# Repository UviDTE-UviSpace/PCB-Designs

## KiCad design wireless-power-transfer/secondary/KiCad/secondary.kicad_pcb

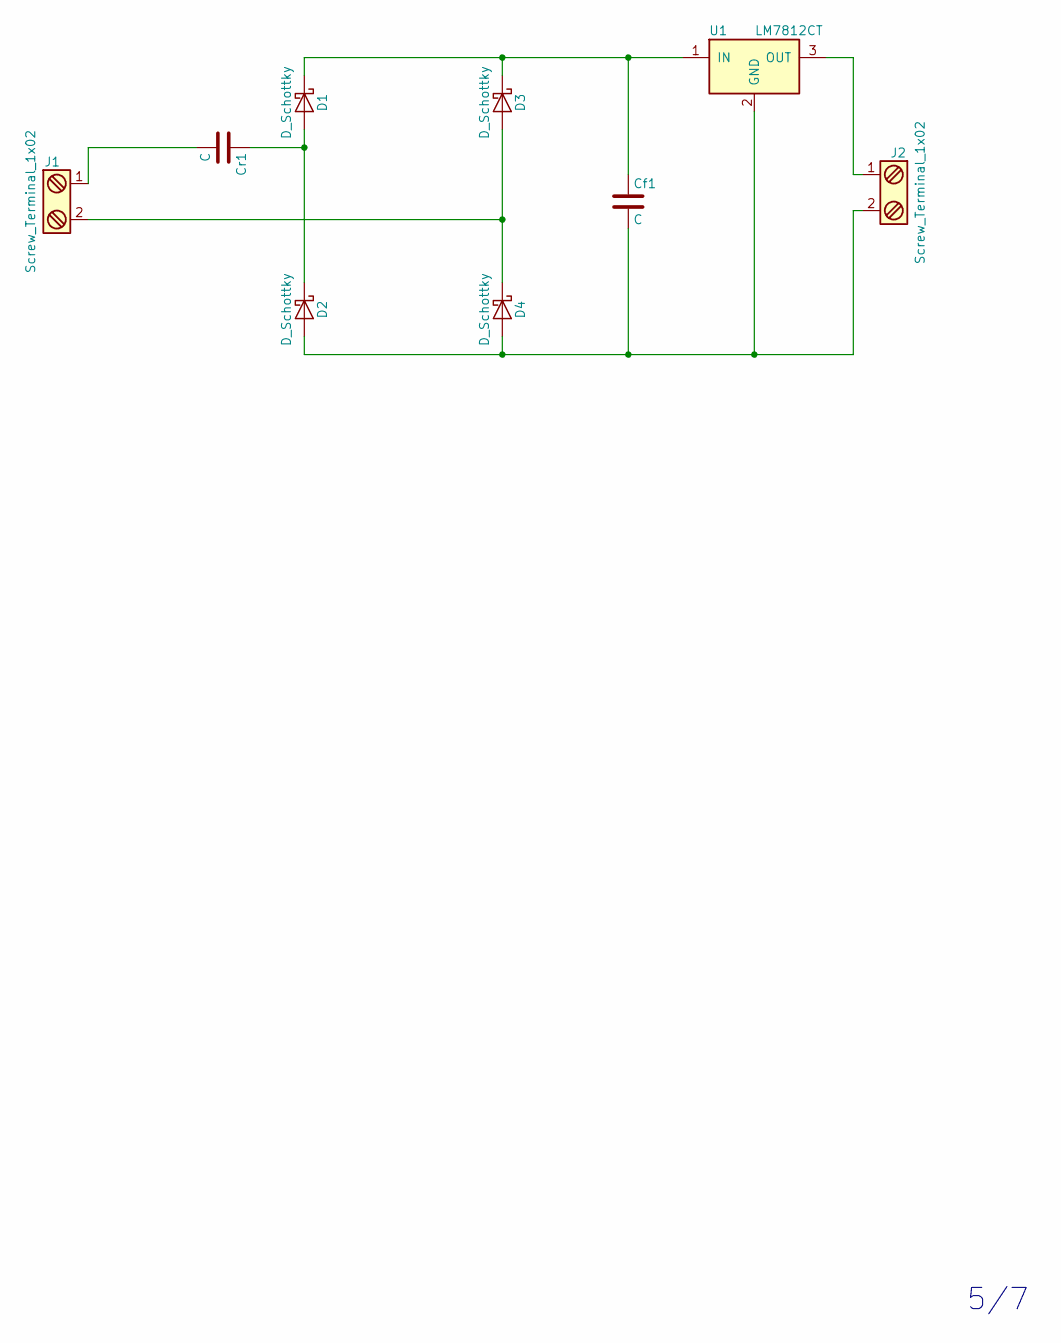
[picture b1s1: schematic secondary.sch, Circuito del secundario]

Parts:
Cf1: C; CP_Radial_D8.0mm_P3.50mm
Cr1: C; C_Axial_L5.1mm_D3.1mm_P7.50mm_Horizontal
D1, D2, D3, D4: D_Schottky; D_DO-201AD_P12.70mm_Horizontal
J1, J2: Screw_Terminal_1x02; TerminalBlock_Pheonix_MKDS1.5-2pol
U1: LM7812CT; TO-220-3_Vertical

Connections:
unnamed: Cf1.1, D1.1 (K), D3.1 (K), U1.1 (IN)
unnamed: Cf1.2, D2.2 (A), D4.2 (A), J2.2, U1.2 (GND)
unnamed: Cr1.1, D1.2 (A), D2.1 (K)
unnamed: Cr1.2, J1.1
unnamed: D3.2 (A), D4.1 (K), J1.2
unnamed: J2.1, U1.3 (OUT)

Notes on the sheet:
5/7

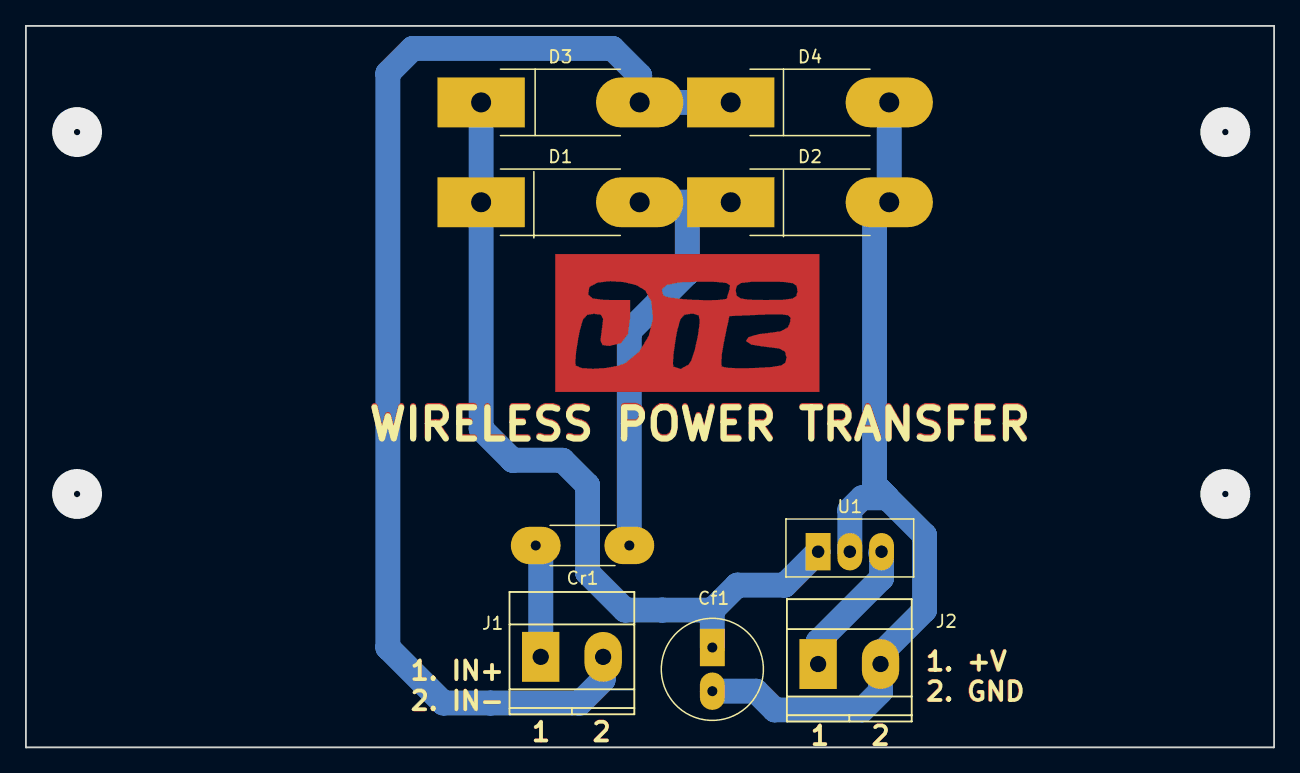
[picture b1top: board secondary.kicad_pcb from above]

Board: 2 copper layers, 100.0 x 57.8 mm, 9 parts (0 on the bottom side), 6 nets.

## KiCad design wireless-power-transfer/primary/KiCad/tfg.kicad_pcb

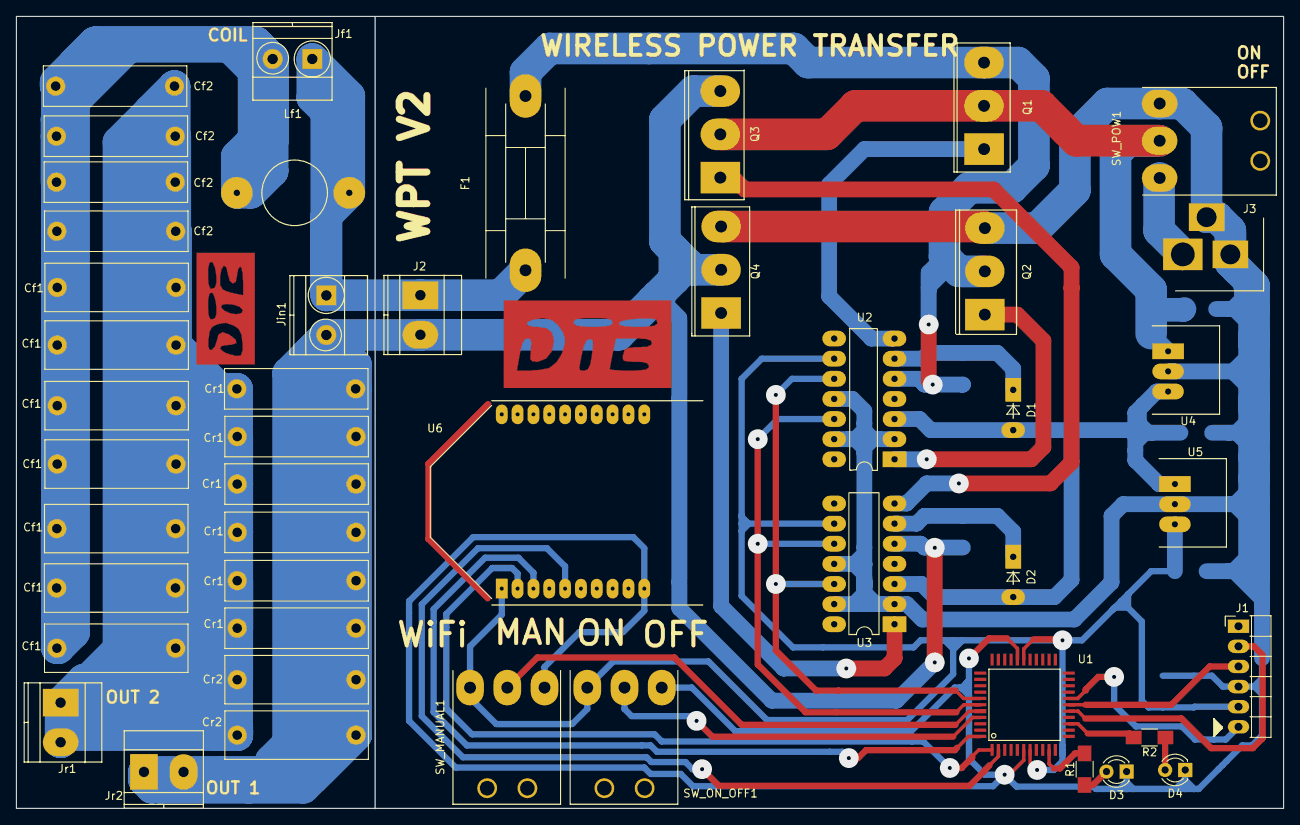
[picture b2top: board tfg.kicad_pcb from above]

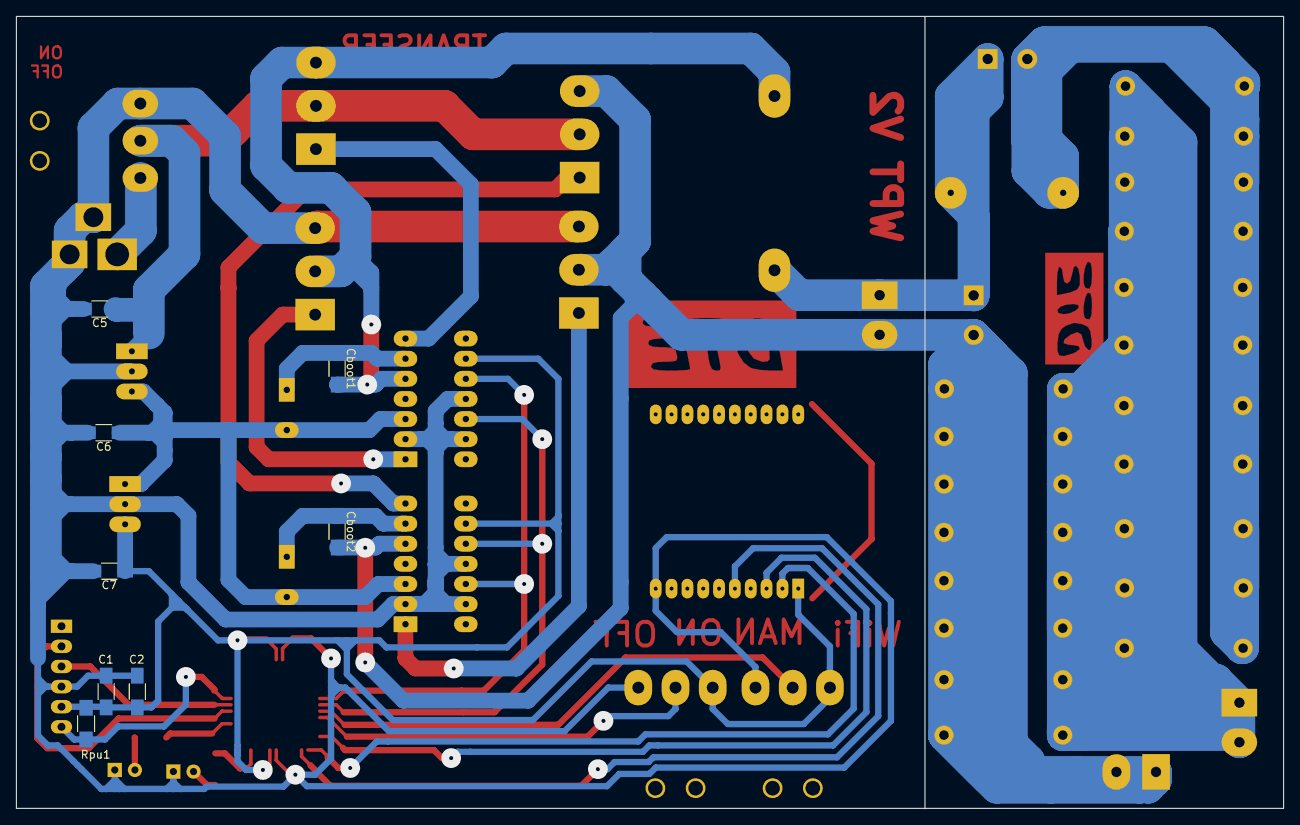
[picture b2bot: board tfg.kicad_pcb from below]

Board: 2 copper layers, 160.0 x 100.0 mm, 55 parts (8 on the bottom side), 31 nets.

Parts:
C1, C2: 0.1uF; C_1206_HandSoldering
C5, C6, C7: 10uF; C_1206_HandSoldering
Cboot1, Cboot2: 0.47uF; C_1206_HandSoldering
Cf1, Cf1#2, Cf1#3, Cf1#4, Cf1#5, Cf1#6, Cf1#7: C; C_Rect_L18.0mm_W6.0mm_P15.00mm_FKS3_FKP3
Cf2, Cf2#2, Cf2#3, Cf2#4: C; C_Rect_L18.0mm_W5.0mm_P15.00mm_FKS3_FKP3
Cr1: C; C_Rect_L18.0mm_W5.0mm_P15.00mm_FKS3_FKP3
Cr1#2, Cr1#3, Cr1#4, Cr1#5, Cr1#6: 100nF; C_Rect_L18.0mm_W5.0mm_P15.00mm_FKS3_FKP3
Cr2: C; C_Rect_L18.0mm_W6.0mm_P15.00mm_FKS3_FKP3
Cr2#2: 10nF; C_Rect_L18.0mm_W6.0mm_P15.00mm_FKS3_FKP3
D1, D2: D; D_DO-35_SOD27_P5.08mm_Vertical_AnodeUp
D3, D4: LED_ALT; LED_D3.0mm
F1: Fuse; Fuseholder5x20_horiz_SemiClosed_Casing10x25mm
J1: CONN_01X06; Pin_Header_Angled_1x06_Pitch2.54mm
J2: Screw_Terminal_1x02; TerminalBlock_Pheonix_MKDS1.5-2pol
J3: BARREL_JACK
Jf1: Screw_Terminal_1x02; TerminalBlock_Pheonix_MKDS1.5-2pol
Jin1: Screw_Terminal_1x02; TerminalBlock_Pheonix_MKDS1.5-2pol
Jr1, Jr2: Screw_Terminal_1x02; TerminalBlock_Pheonix_MKDS1.5-2pol
Lf1: 47uH; MuRata 1500 47u
Q1, Q2, Q3, Q4: IRLB8721PBF; TO-247AC
R1, R2: R; R_1206_HandSoldering
Rpu1: 10k; R_1206_HandSoldering
SW_MANUAL1: SW_SPDT; SPDT_Toggle_Switch
SW_ON_OFF1: SW_SPDT; SPDT_Toggle_Switch
SW_POW1: SW_SPDT; SPDT_Toggle_Switch
U1: PIC18F45K20-I/PT; PIC18F45K20
U2, U3: IR2110; DIP-14_W7.62mm
U4: R-78E15; r-78Exx
U5: R-78E3.3; r-78Exx
U6: XBEE_Wi-Fi; XBee_Wi-Fi

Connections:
/+3.3V: C1.1, C2.1, C7.1, J1.2, Rpu1.2, SW_MANUAL1.1, SW_ON_OFF1.1, U1.7, U1.28, U2.9, U3.9, U5.3, U6.1
/+15V: C6.1, D1.2, D2.2, U2.3, U3.3, U4.3, U5.1
Carga0: Cboot2.2, Cr1.1, Cr2.1, J2.2, Jin1.2, Jr2.1, Jr2.2, Q3.3, Q4.2, U3.5
Carga1: F1.1, J2.1, Jf1.1, Jin1.1, Lf1.1
unnamed: C1.2, C2.2, C5.2, C6.2, C7.2, D3.1, D4.1, J1.3, J3.2, J3.3, Q2.3, Q4.3, SW_MANUAL1.3, SW_ON_OFF1.3, SW_POW1.3, U1.6, U1.29, U2.2, U2.11, U2.13, U3.2, U3.11, U3.13, U4.2, U5.2, U6.10
unnamed: C5.1, Q1.2, Q3.2, SW_POW1.2, U4.1
unnamed: Cboot1.1, D1.1, U2.6
unnamed: Cboot1.2, F1.2, Q1.3, Q2.2, U2.5
unnamed: Cboot2.1, D2.1, U3.6
unnamed: Cf1.1, Cf1#2.1, Cf1#3.1, Cf1#4.1, Cf1#5.1, Cf1#6.1, Cf1#7.1, Cf2.2, Cf2#2.2, Cf2#3.2, Cf2#4.2, Cr1.2, Cr1#2.2, Cr1#3.2, Cr1#4.2, Cr1#5.2, Cr1#6.2, Cr2.2, Cr2#2.2, Jr1.1, Jr1.2
unnamed: Cf1.2, Cf1#2.2, Cf1#3.2, Cf1#4.2, Cf1#5.2, Cf1#6.2, Cf1#7.2, Cf2.1, Cf2#2.1, Cf2#3.1, Cf2#4.1, Jf1.2, Lf1.2
unnamed: Cr1#2.1, Cr1#3.1, Cr1#4.1, Cr1#5.1, Cr1#6.1, Cr2#2.1
unnamed: D3.2, R1.1
unnamed: D4.2, R2.1
unnamed: J1.1, Rpu1.1, U1.18
unnamed: J1.4, U1.17
unnamed: J1.5, U1.16
unnamed: J3.1, SW_POW1.1
unnamed: Q1.1, U2.7
unnamed: Q2.1, U2.1
unnamed: Q3.1, U3.7
unnamed: Q4.1, U3.1
unnamed: R1.2, U1.10
unnamed: R2.2, U1.14
unnamed: SW_MANUAL1.2, U1.40
unnamed: SW_ON_OFF1.2, U1.41
unnamed: U1.1, U6.2
unnamed: U1.2, U6.5
unnamed: U1.38, U2.10, U3.12
unnamed: U1.39, U2.12, U3.10
unnamed: U1.44, U6.3

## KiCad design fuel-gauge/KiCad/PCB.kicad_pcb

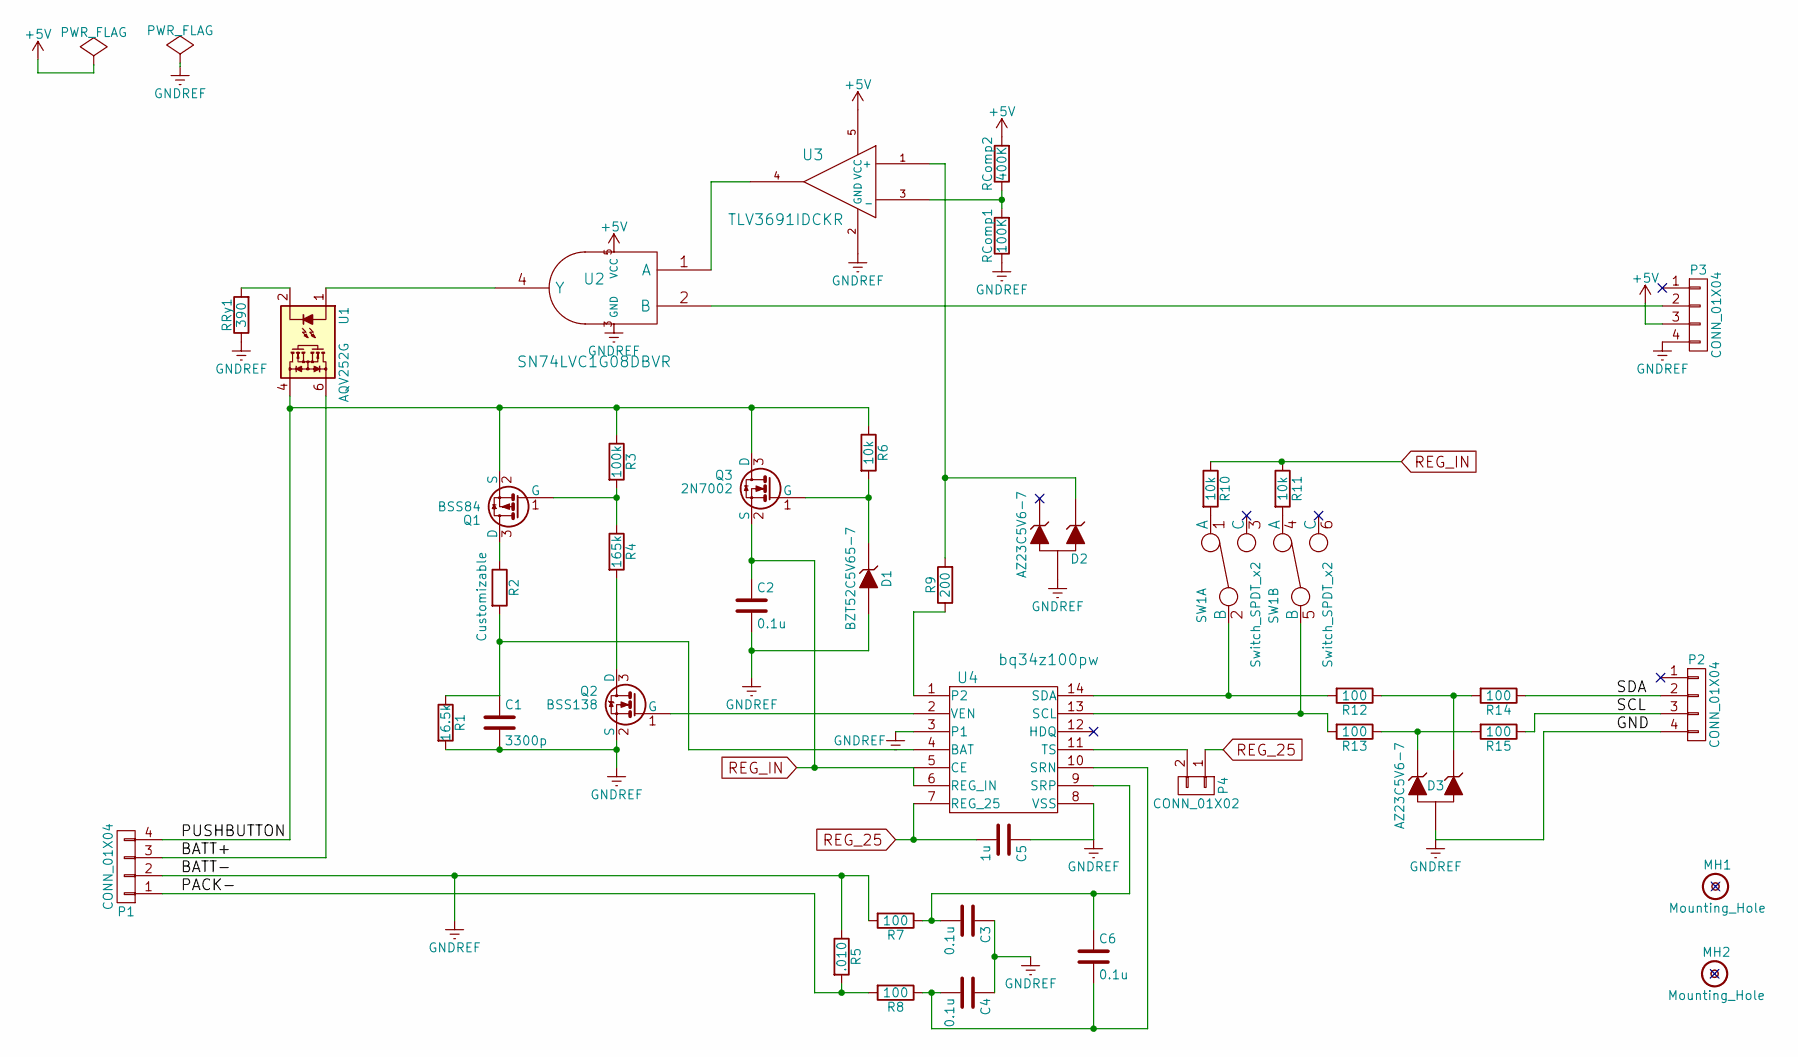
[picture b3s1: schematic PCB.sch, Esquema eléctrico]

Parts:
C1: 3300p; C_0805_HandSoldering
C2, C3, C4, C6: 0.1u; C_0805_HandSoldering
C5: 1u; C_0805_HandSoldering
D1: BZT52C5V65-7; SOD-323
D2, D3: AZ23C5V6-7; D_SOT-23_NKA
MH1, MH2: Mounting_Hole; Mounting_hole
P1, P2, P3: CONN_01X04
P4: CONN_01X02
Q1: BSS84; BSS84-SOT-23_Handsoldering
Q2: BSS138; BSS138-SOT-23_Handsoldering
Q3: 2N7002; SOT-23_Handsoldering
R1: 16.5k; R_0805_My_HandSoldering
R2: Customizable; R_0805_My_HandSoldering
R3: 100k; R_0805_My_HandSoldering
R4: 165k; R_0805_My_HandSoldering
R5: .010; R_2010_My_HandSoldering
R6, R10, R11: 10k; R_0805_My_HandSoldering
R7, R8, R12, R13, R14, R15: 100; R_0805_My_HandSoldering
R9: 200; R_0805_My_HandSoldering
RComp1: 100K; R_0805_My_HandSoldering
RComp2: 400K; R_0805_My_HandSoldering
RRy1: 390; R_0805_My_HandSoldering
SW1: Switch_SPDT_x2; SW1-DIP-8-_6_Handsoldering
U1: AQV252G; DIP-6_W7.62mm
U2: SN74LVC1G08DBVR; SOT-23-5_HandSoldering
U3: TLV3691IDCKR; SC-70-5_Handsoldering
U4: bq34z100pw; SSOP-14-Bq

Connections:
+5V: P3.3, RComp2.2, U2.5 (VCC), U3.5 (VCC)
/BATT+: P1.3, U1.6
/PACK-: P1.1, R5.2, R8.2
/PUSHBUTTON: P1.4, Q1.2 (S), Q3.3 (D), R3.1, R6.1, U1.4
/SCL: P2.3, R15.1
/SDA: P2.2, R14.1
GNDREF: C1.2, C2.2, C3.1, C4.1, C5.1, D1.2 (A), D2.3 (A), D3.3 (A), P1.2, P2.4, P3.4, Q2.2 (S), R1.2, R5.1, R7.2, RComp1.1, RRy1.1, U2.3 (GND), U3.2 (GND), U4.3 (P1), U4.8 (VSS)
unnamed: C1.1, R1.1, R2.2, U4.4 (BAT)
unnamed: C3.2, C6.1, R7.1, U4.9 (SRP)
unnamed: C4.2, C6.2, R8.1, U4.10 (SRN)
unnamed: D1.1 (K), Q3.1 (G), R6.2
unnamed: D2.2 (K), R9.2, U3.1 (+)
unnamed: D3.1 (K), R13.1, R15.2
unnamed: D3.2 (K), R12.1, R14.2
unnamed: P3.2, U2.2 (B)
unnamed: P4.2, U4.11 (TS)
unnamed: Q1.1 (G), R3.2, R4.1
unnamed: Q1.3 (D), R2.1
unnamed: Q2.1 (G), U4.2 (VEN)
unnamed: Q2.3 (D), R4.2
unnamed: R9.1, U4.1 (P2)
unnamed: R10.2, SW1.1 (A)
unnamed: R11.2, SW1.4 (A)
unnamed: R12.2, SW1.2 (B), U4.14 (SDA)
unnamed: R13.2, SW1.5 (B), U4.13 (SCL)
unnamed: RComp1.2, RComp2.1, U3.3 (_)
unnamed: RRy1.2, U1.2
unnamed: U1.1, U2.4 (Y)
unnamed: U2.1 (A), U3.4
REG_25: C5.2, P4.1, U4.7 (REG_25)
REG_IN: C2.1, Q3.2 (S), R10.1, R11.1, U4.5 (CE), U4.6 (REG_IN)

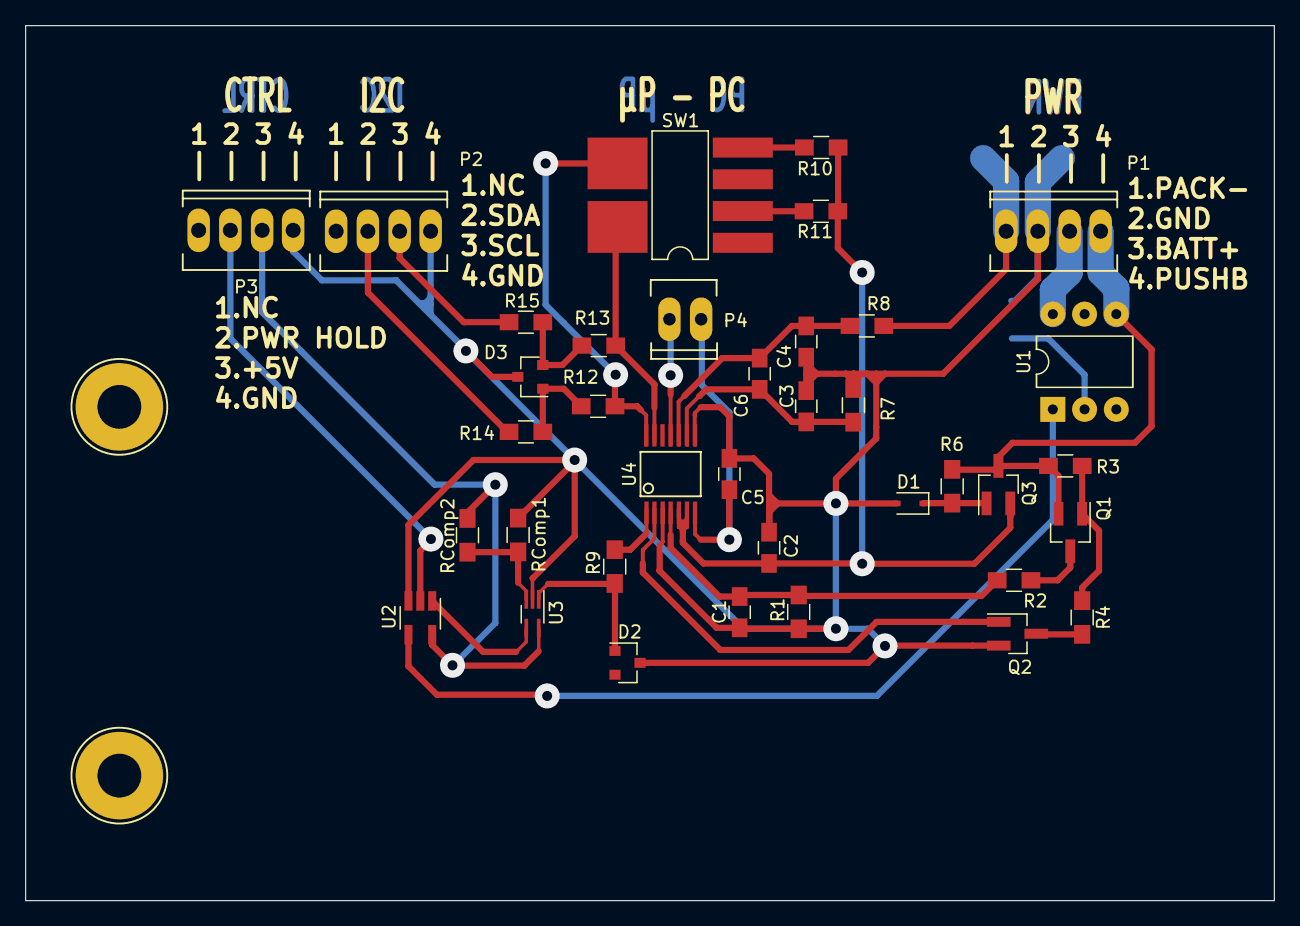
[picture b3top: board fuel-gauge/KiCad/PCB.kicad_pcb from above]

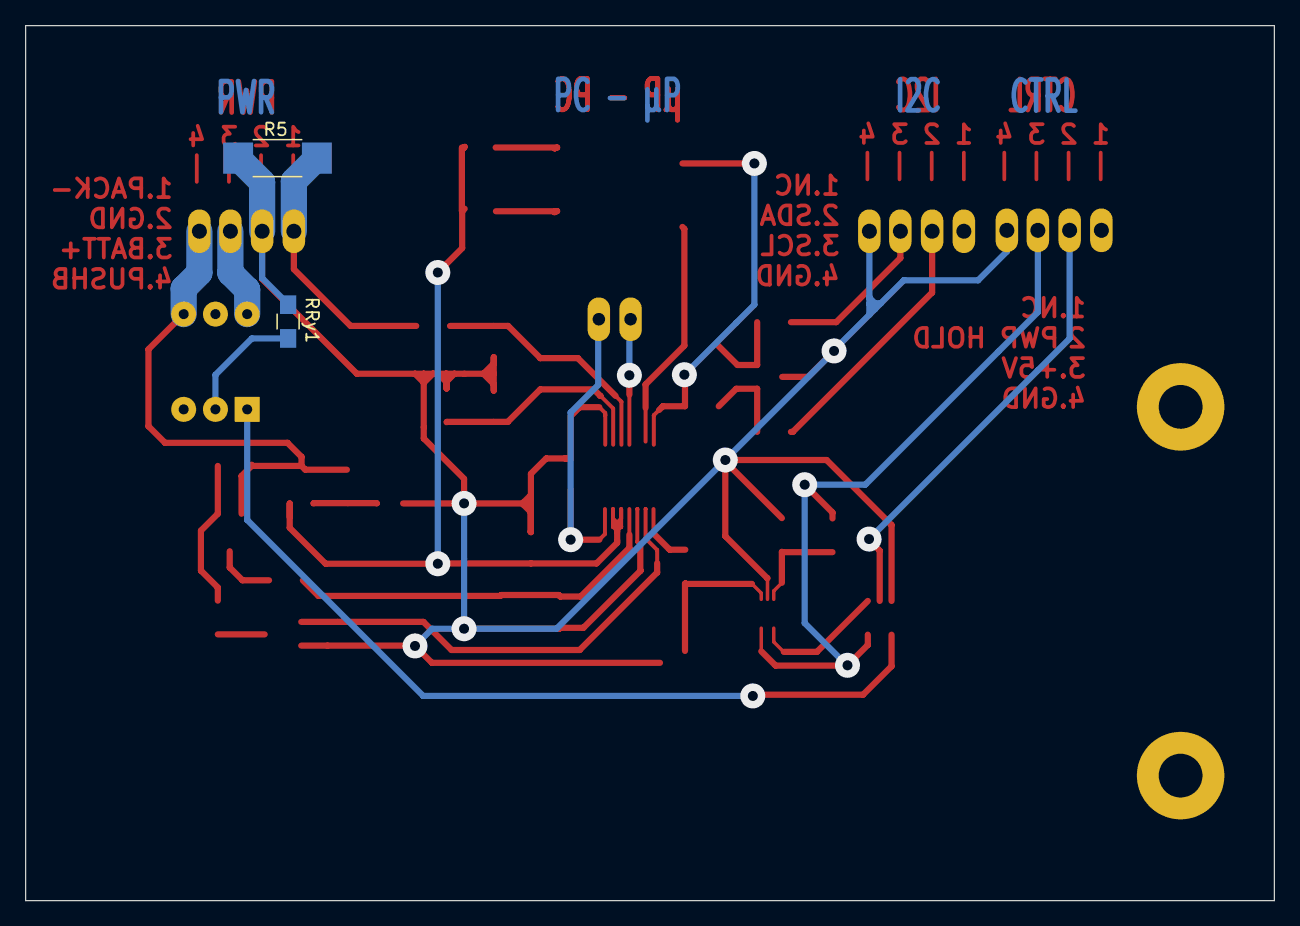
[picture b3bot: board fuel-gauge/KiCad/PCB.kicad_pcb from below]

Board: 2 copper layers, 99.9 x 70.0 mm, 41 parts (2 on the bottom side), 31 nets.

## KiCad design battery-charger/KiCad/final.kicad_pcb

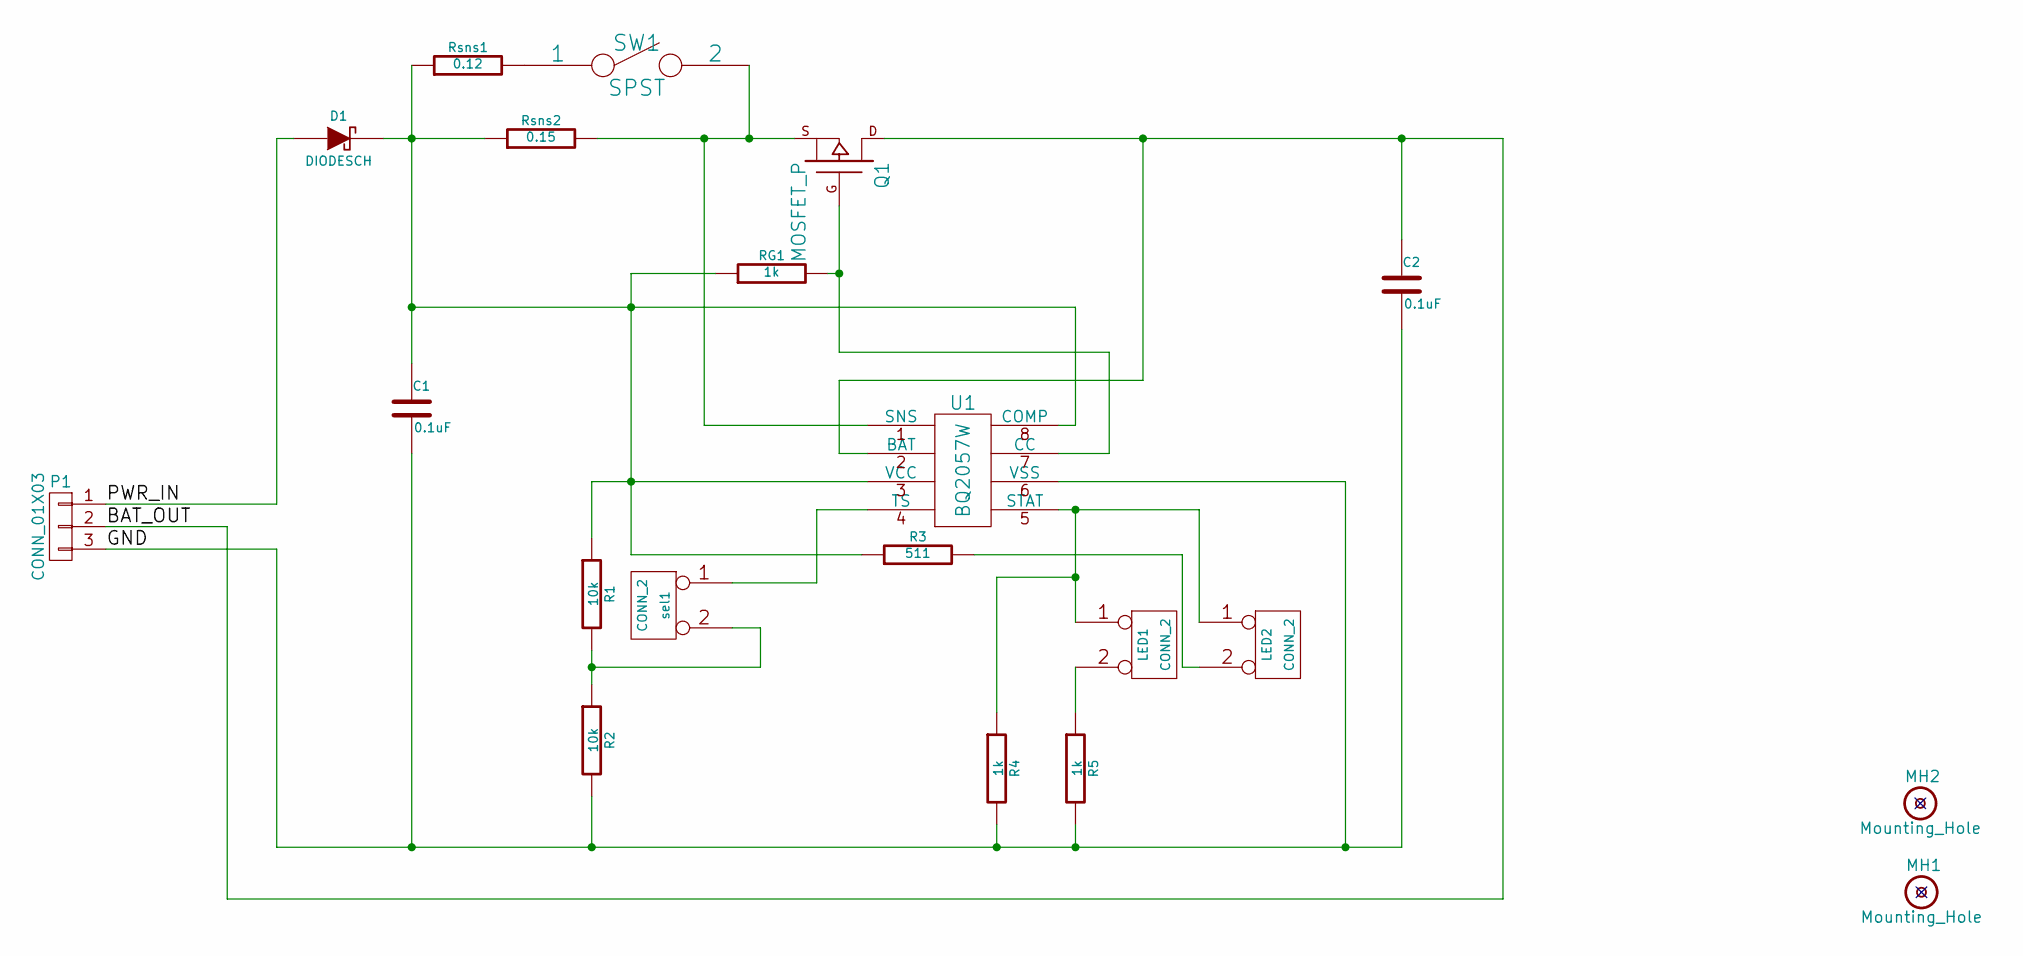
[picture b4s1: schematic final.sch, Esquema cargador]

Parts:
C1, C2: 0.1uF; C_0603
D1: DIODESCH; D_DO-201AD
LED1, LED2: CONN_2; Molex_02x01
MH1, MH2: Mounting_Hole; Mounting_hole
P1: CONN_01X03; Molex_03x01_Straight
Q1: MOSFET_P; TO-220-3
R1, R2: 10k; R_THT_0.54
R3: 511; R_THT_0.54
R4, R5: 1k; R_THT_0.78
RG1: 1k; R_THT_0.78
Rsns1: 0.12; R_2512_HandSoldering
Rsns2: 0.15; R_2512_HandSoldering
SW1: SPST; Switch
U1: BQ2057W; SOIC-8_Handsoldering
sel1: CONN_2; Pin_Header_Straight_01x02

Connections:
/BAT_OUT: C2.1, P1.2, Q1.D, U1.2 (BAT)
/GND: C1.2, C2.2, P1.3, R2.2, R4.2, R5.2, U1.6 (VSS)
/PWR_IN: D1.1 (A), P1.1
unnamed: C1.1, D1.2 (K), R1.1, R3.1, RG1.1, Rsns1.1, Rsns2.1, U1.3 (VCC), U1.8 (COMP)
unnamed: LED1.1, LED2.1, R4.1, U1.5 (STAT)
unnamed: LED1.2 (PM), R5.1
unnamed: LED2.2 (PM), R3.2
unnamed: Q1.G, RG1.2, U1.7 (CC)
unnamed: Q1.S, Rsns2.2, SW1.2, U1.1 (SNS)
unnamed: R1.2, R2.1, sel1.2 (PM)
unnamed: Rsns1.2, SW1.1
unnamed: U1.4 (TS), sel1.1

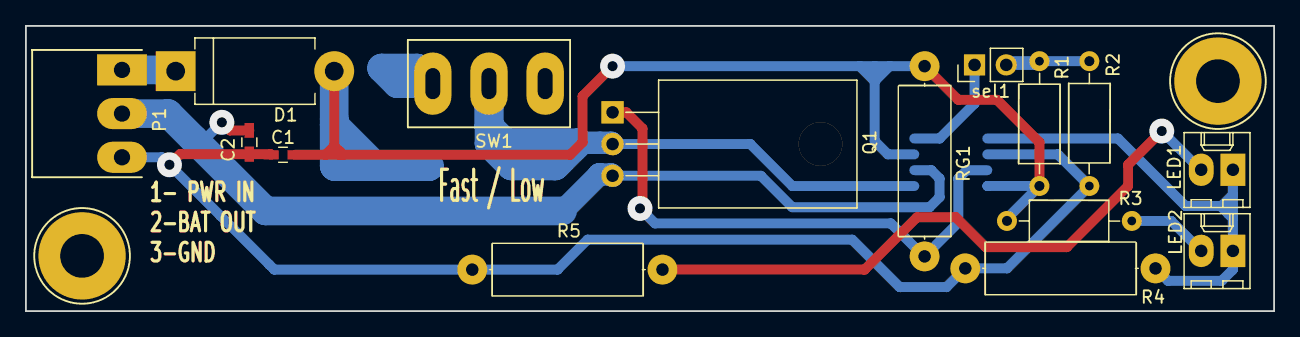
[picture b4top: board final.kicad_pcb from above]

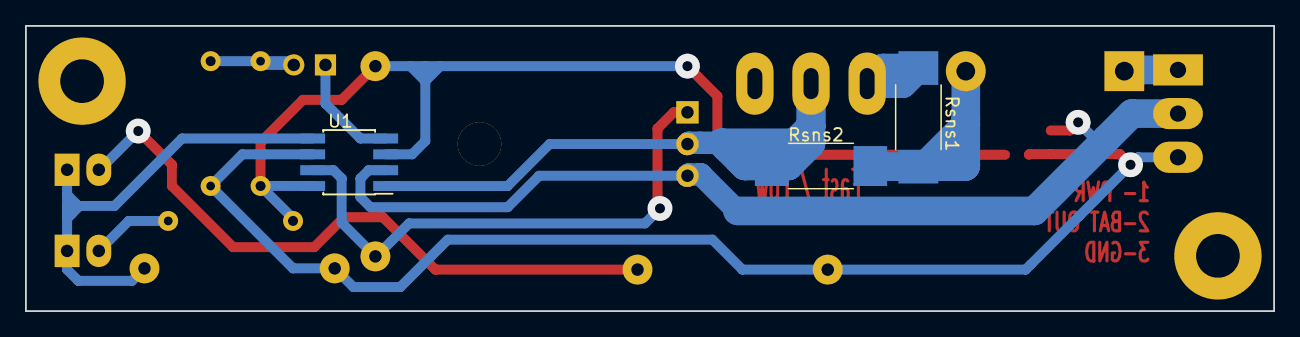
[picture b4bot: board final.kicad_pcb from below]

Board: 2 copper layers, 100.0 x 22.8 mm, 20 parts (3 on the bottom side), 12 nets.

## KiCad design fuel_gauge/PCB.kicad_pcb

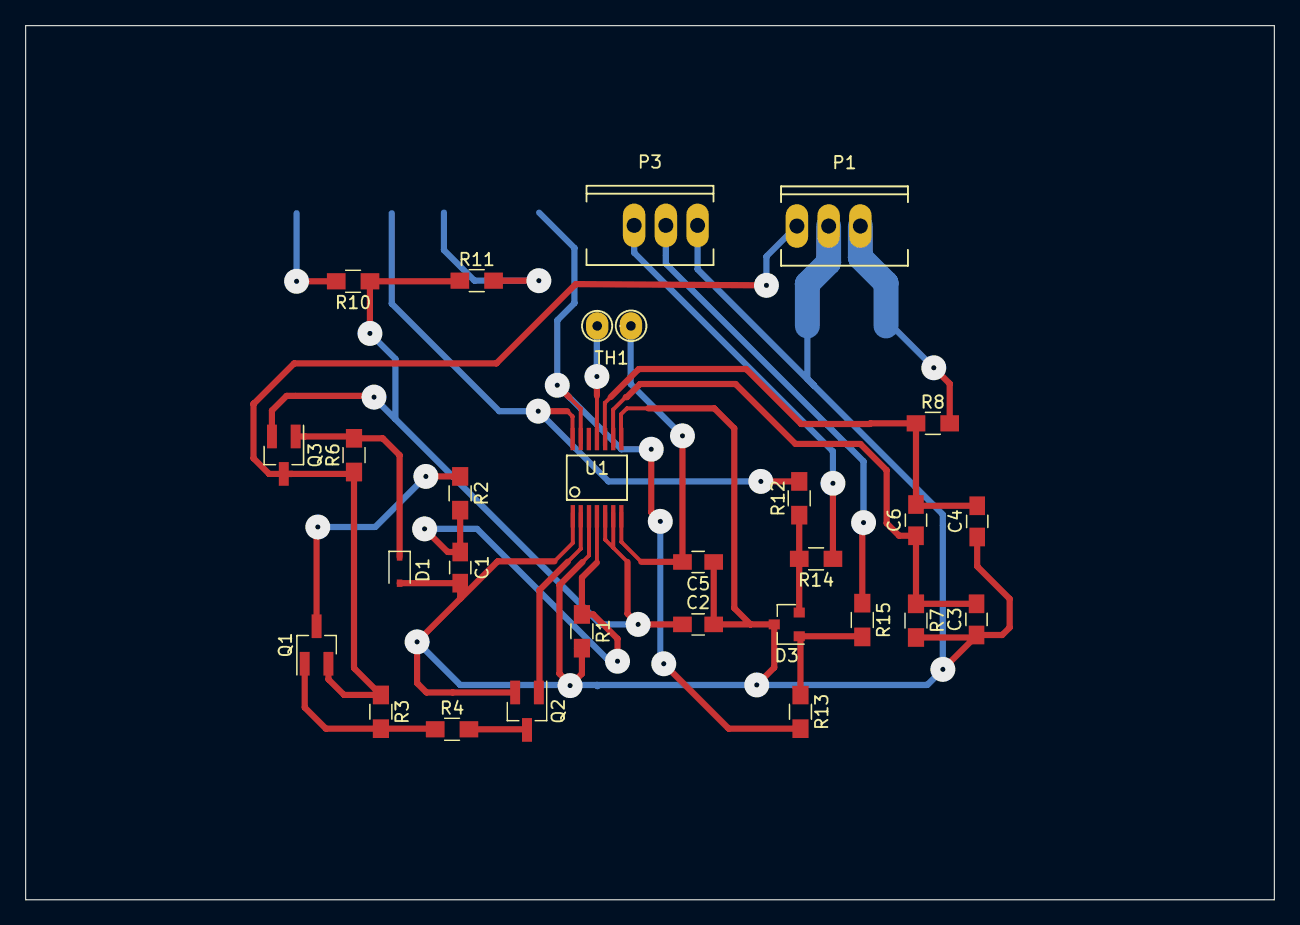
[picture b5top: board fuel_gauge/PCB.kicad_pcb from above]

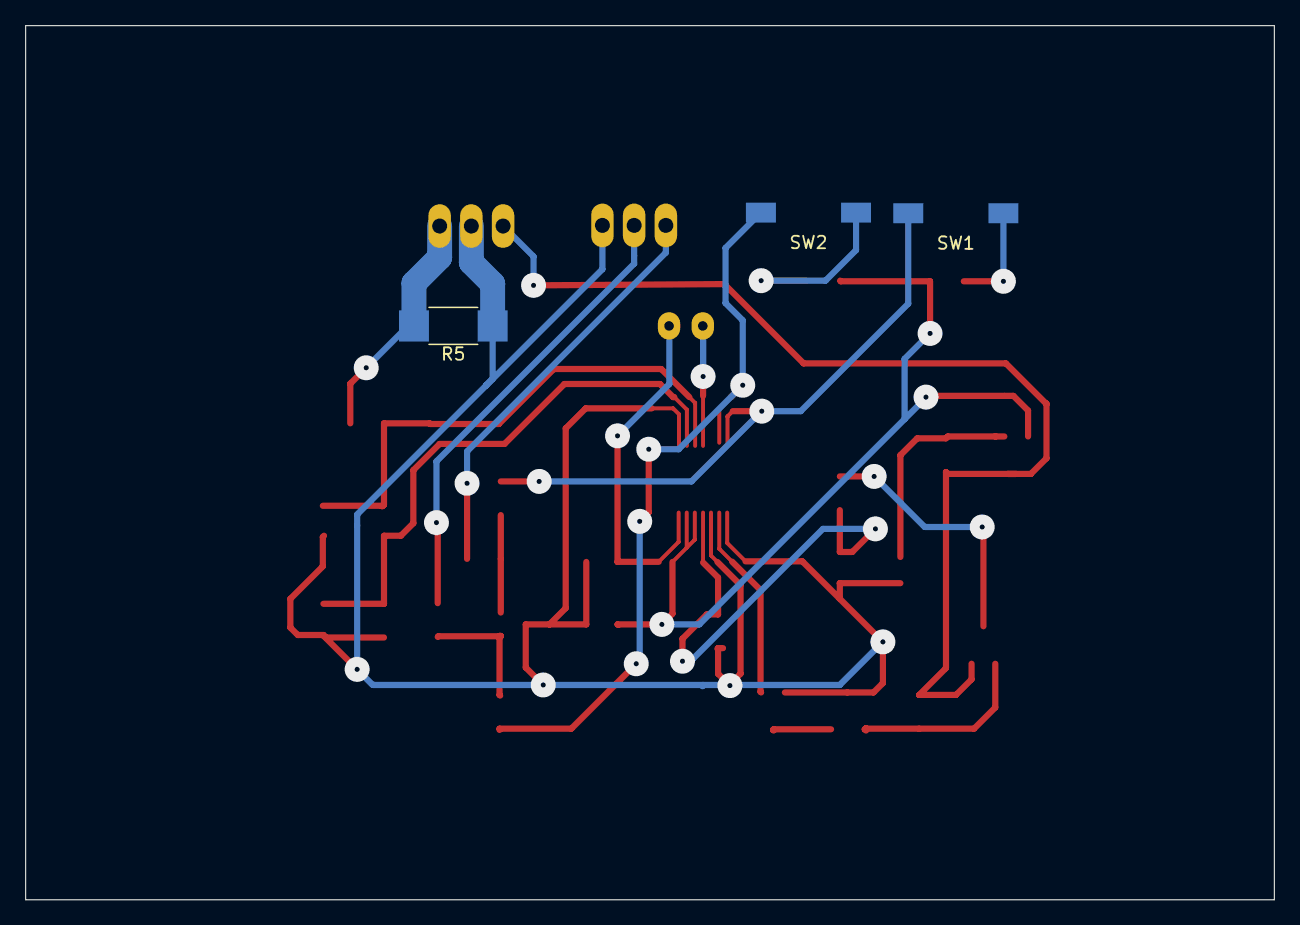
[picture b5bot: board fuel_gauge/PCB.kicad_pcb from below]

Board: 2 copper layers, 100.0 x 70.0 mm, 31 parts (3 on the bottom side), 22 nets.

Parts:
C1: 3300p; C_0805_HandSoldering
C2, C3, C4, C6: 0.1u; C_0805_HandSoldering
C5: 1u; C_0805_HandSoldering
D1: BZT52C5V65-7; SOD-323
D3: AZ23C5V6-7; D_SOT-23_NKA
P1: Con3,123*; Con3,123-
P3: Con3,*234; Con3,-234
Q1: BSS84; BSS84-SOT-23_Handsoldering
Q2: BSS138; BSS138-SOT-23_Handsoldering
Q3: 2N7002; SOT-23_Handsoldering
R1: 16.5k; R_0805_My_HandSoldering
R2: Customizable; R_0805_My_HandSoldering
R3: 100k; R_0805_My_HandSoldering
R4: 165k; R_0805_My_HandSoldering
R5: .010; R_2010_My_HandSoldering
R6, R10, R11: 10k; R_0805_My_HandSoldering
R7, R8, R12, R13, R14, R15: 100; R_0805_My_HandSoldering
SW1, SW2: SPST; DIP-2_LongPads
TH1: 10K; Thermistor
U1: bq34z100pw; SSOP-14-Bq

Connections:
/BATT+: P1.1, Q1.2, Q3.3, R3.1, R6.1
/PACK-: P1.3, R5.2, R8.2
/SCL: P3.3, R15.1
/SDA: P3.2, R14.1
GNDREF: C1.2, C2.2, C3.1, C4.1, C5.1, D1.2, D3.3, P1.2, P3.4, Q2.2, R1.2, R5.1, R7.2, U1.1, U1.3, U1.8
unnamed: C1.1, R1.1, R2.2, U1.4
unnamed: C3.2, C6.1, R7.1, U1.9
unnamed: C4.2, C6.2, R8.1, U1.10
unnamed: D1.1, Q3.1, R6.2
unnamed: D3.1, R12.1, R14.2
unnamed: D3.2, R13.1, R15.2
unnamed: Q1.1, R3.2, R4.1
unnamed: Q1.3, R2.1
unnamed: Q2.1, U1.2
unnamed: Q2.3, R4.2
unnamed: R10.2, SW1.1
unnamed: R11.2, SW2.1
unnamed: R12.2, SW1.2, U1.14
unnamed: R13.2, SW2.2, U1.13
unnamed: TH1.2, U1.11
REG_25: C5.2, TH1.1, U1.7
REG_IN: C2.1, Q3.2, R10.1, R11.1, U1.5, U1.6

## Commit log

2017-07-18 Initial project version
2017-07-24 Remove unnecessary files
2017-07-24 Rename folders
2017-09-29 Add library into a separated folder named component-library
    Add switches to select PC or Arduino communications
2017-10-06 add battery charger to the project
2017-10-10 put names in english
2017-10-10 First version of primary circuit for wpt charger
2017-10-16 First version of the PCB
2017-10-18 New version with changed interruptors, improved routing layout, fixed 3d designs and Wi-Fi module, among other minor changes
2017-10-18 New version with changed interruptors, improved routing layout, fixed 3d designs and Wi-Fi module, among other minor changes.
2017-10-18 Schematic of the secondary side added.
2017-10-19 First version of the secondary PCB
2017-10-19 Orientation of the primary coil connector fixed.
2017-10-19 LEDs for power and charging indication added.
2017-10-19 Gerber files added.
2017-10-19 fixed MOSFET sizes and some excessively small pads.
2017-10-20 Fixed some pads size.
2017-10-20 Added folder for memory diagrams and schematics sheets for primary, secondary and power diagram.
2017-10-20 Add the Degree's Thesis to the repository
2017-10-20 Added pdf sheets and modified layout according with the school standard for TFGs.
2017-10-23 Modified traces for giving some margin to the edges of the board.
2017-10-25 Power circuit diagram modified with some text-based explanations.
2017-10-25 PCB modified extracting the filter and the tank to another PCB.
2017-10-25 Added switch labels.
2017-10-26 Update the PCB design
2017-10-26 Added pcb with tank and filter of the primary, some logos and other minor changes.
2017-10-27 Modified secondary PCB for better fitting in the car.
2017-10-27 Change directory names and give the repository an structure
    Include some changes in the pcb design of the fuel gauge
2017-10-27 modified pad sizes and secondary PCB layout.
2017-10-30 Added a second connector for resonant coil of the primary.
2017-10-30 Minor changes.
2017-10-31 Update fuel gauge pcb design to the v2
2017-10-31 Switch moved because of the proximity to the connector.
2017-10-31 add the pcb fabrication pdf files and rename schematic pdf
2017-11-02 Correct the footprint of the switch 1
2017-11-02 Update the design to the v2
    Include new routing to minimize the number of vias used and some
    electrical considerations. Also the names of the connectors and the
    positions of the switch.
2017-11-02 Include PCB pdfs
2017-11-02 Clean charger repository in order to give the same structure to both, charger and fuel-gauge.
2017-11-07 Modified pin widths of the microcontroller and distance between paths and borders
2017-11-07 Modified distance to edges and microcontroller pin's widht.
2017-11-07 add pdf of the pcb of the primary v1 that was manufactured
2017-11-10 Add the Bill Of Materials of the fuel gauge PCB v2.0 with the dealer reference
2017-11-10 Give a defined structure to a folder into the repository
2017-11-13 Improve pcb design readability relocating references and values.
    Also rename some files to be coherent with the repository.
2017-11-13 Include PCB pdfs
    Also rename some files to be coherent with the repository
2017-11-13 PCB size modified. Added marks for mounting holes.
2017-11-13 Give coherency to the battery charger folder
    Also link correctly the schematics library with relative routes
2017-11-13 Fix error in the library component route
2017-11-14 Modify the circuit in order to fit with the UGV v2.0 wiring
2017-11-15 Correct SW1 positions and PWR connections
    SW1 was well placed and wired but the text in copper layer that explains
    the two posible positions was wrong.
    PWR connector was wrong wired. Now all the circuit on the board is
    supplied by the PUSHBUTTON terminal. In this way, when either the
    Arduino, either the fuel gauge shut down the UGV, all the circuitry will
    shut down.
2017-11-15 Add and relocate names in copper layers and update pdfs
2017-11-15 Save the fuel gauge v2.0
    This version of the PCB was tested. The bq integrated circuit works well
    as so as the alert.
2017-11-16 Change a component and redesign drills
    The thermistor is sustituted by a connector in order to have no wirings
    in the PCB. The thermistor has to be located near the battery.
    Drills were redesign in orther to create a correct version to send to a
    PCB manufacturer.
2017-11-16 Second version of primary PCB.
2017-11-16 Link correctly the specific footprint library
2017-11-16 Link correctly the specific footprint library and change one component
    The two connectors are repleaced by a 3-pin connector in order to reduce
    length of power traces.
2017-11-17 Added resistor between pins 1 and 2 of the PicKit connector.
2017-11-20 Update the v2.0 of the battery charger PCB
    Include the Bill of Materials (BOM) with all the components
    Include all the footprints in the footprint library
2017-11-20 Update the v2.0 of the fuel gauge PCB
    Include the Bill of Materials (BOM) with all the components
    Include the new footprint of the mounting hole
2017-11-20 Fix an error with libraries paths
2017-11-20 Fix an error with footprint library
2017-11-21 The two PCBs of the primary circuit have been connected.
2017-11-22 Minor changes on Silk layer.
2017-11-27 Prepare Silk Layer in order to be able to manufacture
    This 'manu2' branch was created in order to have the 3 projects
    on the same folder.
    The silk layer was created and adapted to give it to an external
    manufacturer.
    Nearly the same information was created in the copper layer in order to
    have this information also in the case the PCB's were manufactured in
2017-11-27 Fix some errors in the border of boards to panelize them correctly
2017-12-12 Include golden image for programming new fuel gauges
    Also include the drivers for the EV2300 Interface board for 32 bit Windows 7
2018-02-08 Adding some drawings.
2018-02-15 PDFs created with schematics and PCB layers for front and back sides.
2018-03-06 Arranged component-library
2018-03-12 Schematics and footprint libraries ready
2018-03-12 Secondary libraries arranged
2018-04-17 Added TFG-wpt-system document to the repository.
